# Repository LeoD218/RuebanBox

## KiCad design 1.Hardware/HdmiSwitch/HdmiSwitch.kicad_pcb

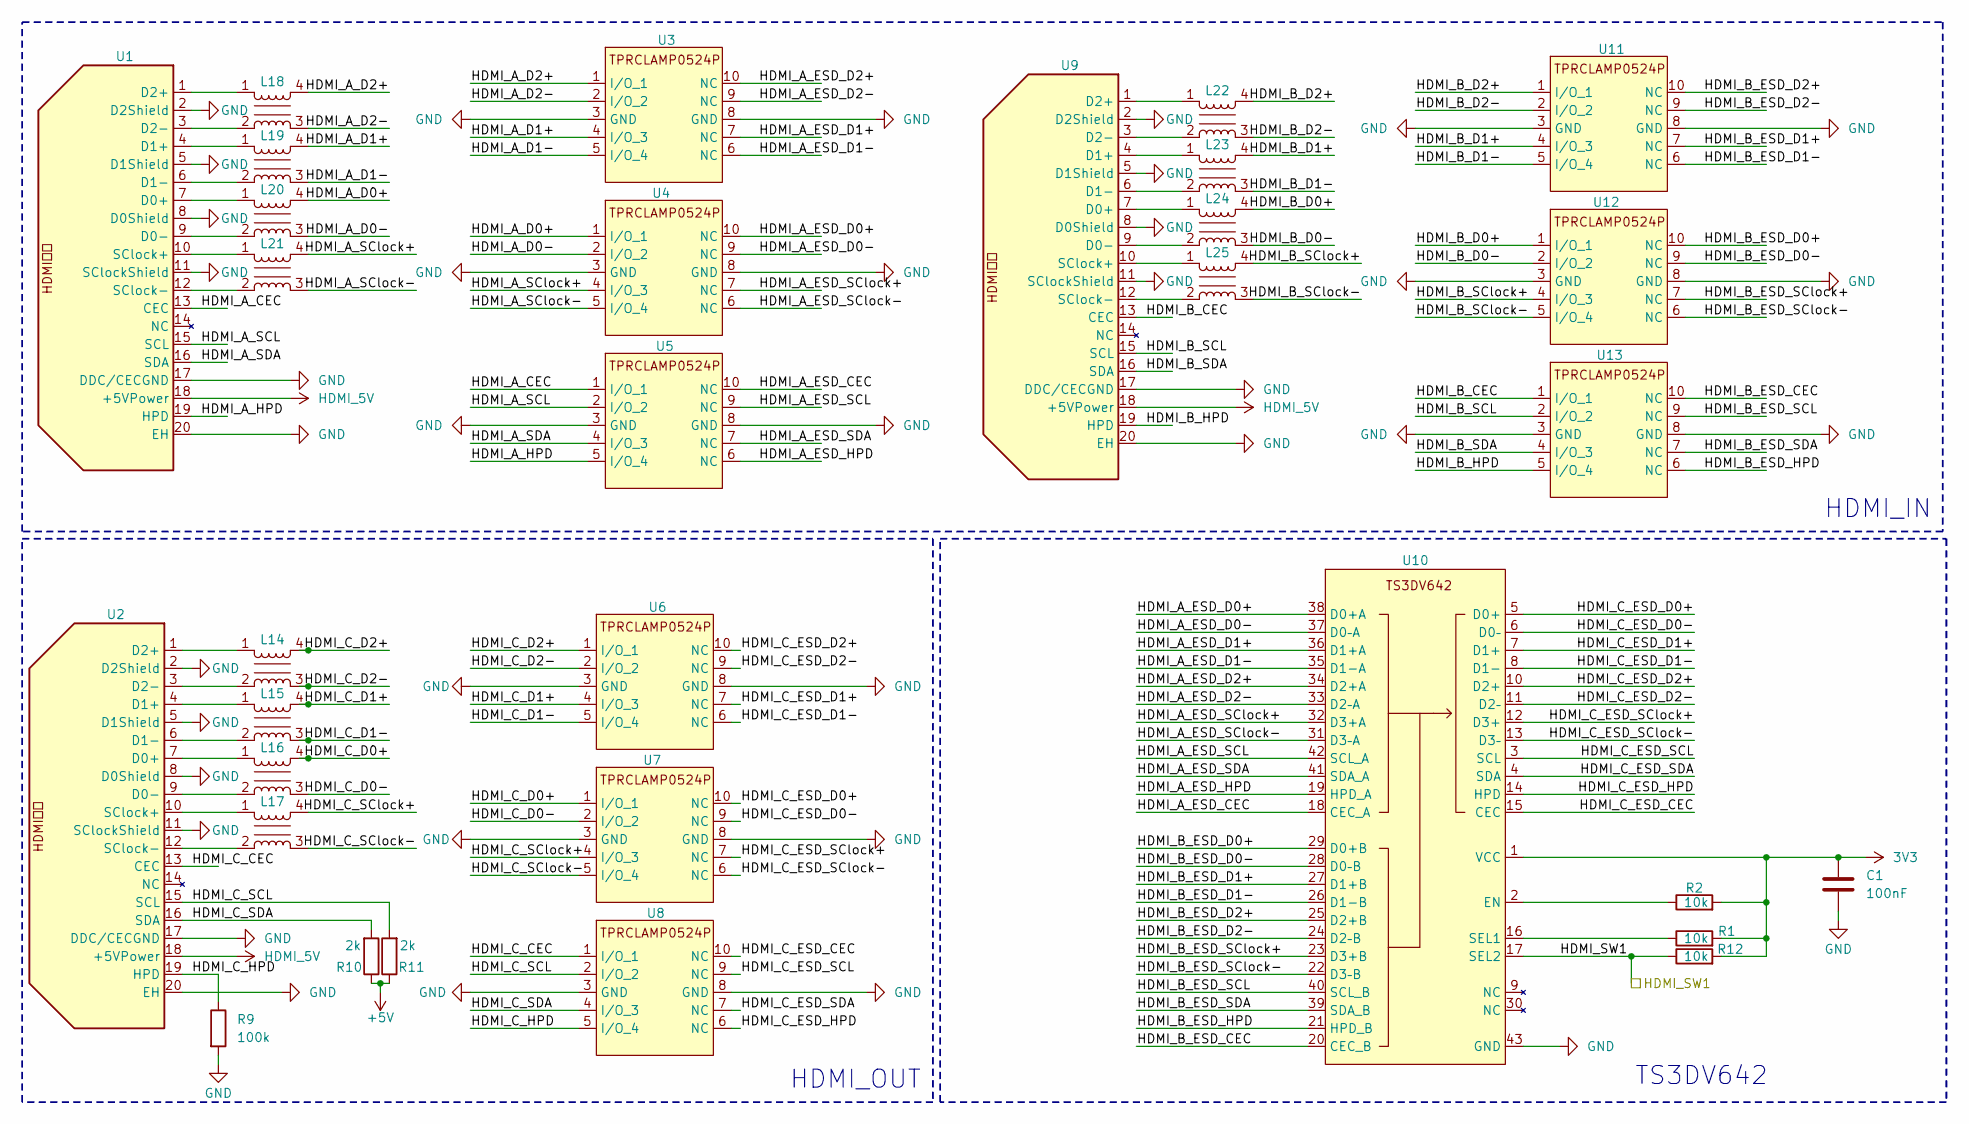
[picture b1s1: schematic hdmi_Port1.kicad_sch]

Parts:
C1: 100nF; C_0402_1005Metric
L14, L15, L16, L17, L18, L19, L20, L21, L22, L23, L24, L25: ACM2012-900-2P-T002
R1, R2: 10k; R_0402_1005Metric
R9: 100k; R_0402_1005Metric
R10, R11: 2k; R_0402_1005Metric
R12: 10k; C_0402_1005Metric
U1, U2, U9: HDMI侧插
U3, U4, U5, U6, U7, U8, U11, U12, U13: TPRCLAMP0524P
U10: TS3DV642

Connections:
3V3: C1.1, R1.2, R2.2, R12.2, U10.1 (VCC); also elsewhere on the board
+5V: R10.1, R11.1; also elsewhere on the board
/hdmi_Port1/HDMI_A_CEC: U1.13 (CEC), U5.1 (I/O_1)
/hdmi_Port1/HDMI_A_D0+: L20.4, U4.1 (I/O_1)
/hdmi_Port1/HDMI_A_D0-: L20.3, U4.2 (I/O_2)
/hdmi_Port1/HDMI_A_D1+: L19.4, U3.4 (I/O_3)
/hdmi_Port1/HDMI_A_D1-: L19.3, U3.5 (I/O_4)
/hdmi_Port1/HDMI_A_D2+: L18.4, U3.1 (I/O_1)
/hdmi_Port1/HDMI_A_D2-: L18.3, U3.2 (I/O_2)
/hdmi_Port1/HDMI_A_ESD_CEC: U5.10 (NC), U10.18 (CEC_A)
/hdmi_Port1/HDMI_A_ESD_D0+: U4.10 (NC), U10.38 (D0+A)
/hdmi_Port1/HDMI_A_ESD_D0-: U4.9 (NC), U10.37 (D0–A)
/hdmi_Port1/HDMI_A_ESD_D1+: U3.7 (NC), U10.36 (D1+A)
/hdmi_Port1/HDMI_A_ESD_D1-: U3.6 (NC), U10.35 (D1-A)
/hdmi_Port1/HDMI_A_ESD_D2+: U3.10 (NC), U10.34 (D2+A)
/hdmi_Port1/HDMI_A_ESD_D2-: U3.9 (NC), U10.33 (D2–A)
/hdmi_Port1/HDMI_A_ESD_HPD: U5.6 (NC), U10.19 (HPD_A)
/hdmi_Port1/HDMI_A_ESD_SCL: U5.9 (NC), U10.42 (SCL_A)
/hdmi_Port1/HDMI_A_ESD_SClock+: U4.7 (NC), U10.32 (D3+A)
/hdmi_Port1/HDMI_A_ESD_SClock-: U4.6 (NC), U10.31 (D3–A)
/hdmi_Port1/HDMI_A_ESD_SDA: U5.7 (NC), U10.41 (SDA_A)
/hdmi_Port1/HDMI_A_HPD: U1.19 (HPD), U5.5 (I/O_4)
/hdmi_Port1/HDMI_A_SCL: U1.15 (SCL), U5.2 (I/O_2)
/hdmi_Port1/HDMI_A_SClock+: L21.4, U4.4 (I/O_3)
/hdmi_Port1/HDMI_A_SClock-: L21.3, U4.5 (I/O_4)
/hdmi_Port1/HDMI_A_SDA: U1.16 (SDA), U5.4 (I/O_3)
/hdmi_Port1/HDMI_B_CEC: U9.13 (CEC), U13.1 (I/O_1)
/hdmi_Port1/HDMI_B_D0+: L24.4, U12.1 (I/O_1)
/hdmi_Port1/HDMI_B_D0-: L24.3, U12.2 (I/O_2)
/hdmi_Port1/HDMI_B_D1+: L23.4, U11.4 (I/O_3)
/hdmi_Port1/HDMI_B_D1-: L23.3, U11.5 (I/O_4)
/hdmi_Port1/HDMI_B_D2+: L22.4, U11.1 (I/O_1)
/hdmi_Port1/HDMI_B_D2-: L22.3, U11.2 (I/O_2)
/hdmi_Port1/HDMI_B_ESD_CEC: U10.20 (CEC_B), U13.10 (NC)
/hdmi_Port1/HDMI_B_ESD_D0+: U10.29 (D0+B), U12.10 (NC)
/hdmi_Port1/HDMI_B_ESD_D0-: U10.28 (D0–B), U12.9 (NC)
/hdmi_Port1/HDMI_B_ESD_D1+: U10.27 (D1+B), U11.7 (NC)
/hdmi_Port1/HDMI_B_ESD_D1-: U10.26 (D1-B), U11.6 (NC)
/hdmi_Port1/HDMI_B_ESD_D2+: U10.25 (D2+B), U11.10 (NC)
/hdmi_Port1/HDMI_B_ESD_D2-: U10.24 (D2–B), U11.9 (NC)
/hdmi_Port1/HDMI_B_ESD_HPD: U10.21 (HPD_B), U13.6 (NC)
/hdmi_Port1/HDMI_B_ESD_SCL: U10.40 (SCL_B), U13.9 (NC)
/hdmi_Port1/HDMI_B_ESD_SClock+: U10.23 (D3+B), U12.7 (NC)
/hdmi_Port1/HDMI_B_ESD_SClock-: U10.22 (D3–B), U12.6 (NC)
/hdmi_Port1/HDMI_B_ESD_SDA: U10.39 (SDA_B), U13.7 (NC)
/hdmi_Port1/HDMI_B_HPD: U9.19 (HPD), U13.5 (I/O_4)
/hdmi_Port1/HDMI_B_SCL: U9.15 (SCL), U13.2 (I/O_2)
/hdmi_Port1/HDMI_B_SClock+: L25.4, U12.4 (I/O_3)
/hdmi_Port1/HDMI_B_SClock-: L25.3, U12.5 (I/O_4)
/hdmi_Port1/HDMI_B_SDA: U9.16 (SDA), U13.4 (I/O_3)
/hdmi_Port1/HDMI_C_CEC: U2.13 (CEC), U8.1 (I/O_1)
/hdmi_Port1/HDMI_C_D0+: L16.4, U7.1 (I/O_1)
/hdmi_Port1/HDMI_C_D0-: L16.3, U7.2 (I/O_2)
/hdmi_Port1/HDMI_C_D1+: L15.4, U6.4 (I/O_3)
/hdmi_Port1/HDMI_C_D1-: L15.3, U6.5 (I/O_4)
/hdmi_Port1/HDMI_C_D2+: L14.4, U6.1 (I/O_1)
/hdmi_Port1/HDMI_C_D2-: L14.3, U6.2 (I/O_2)
/hdmi_Port1/HDMI_C_ESD_CEC: U8.10 (NC), U10.15 (CEC)
/hdmi_Port1/HDMI_C_ESD_D0+: U7.10 (NC), U10.5 (D0+)
/hdmi_Port1/HDMI_C_ESD_D0-: U7.9 (NC), U10.6 (D0–)
/hdmi_Port1/HDMI_C_ESD_D1+: U6.7 (NC), U10.7 (D1+)
/hdmi_Port1/HDMI_C_ESD_D1-: U6.6 (NC), U10.8 (D1-)
/hdmi_Port1/HDMI_C_ESD_D2+: U6.10 (NC), U10.10 (D2+)
/hdmi_Port1/HDMI_C_ESD_D2-: U6.9 (NC), U10.11 (D2–)
/hdmi_Port1/HDMI_C_ESD_HPD: U8.6 (NC), U10.14 (HPD)
/hdmi_Port1/HDMI_C_ESD_SCL: U8.9 (NC), U10.3 (SCL)
/hdmi_Port1/HDMI_C_ESD_SClock+: U7.7 (NC), U10.12 (D3+)
/hdmi_Port1/HDMI_C_ESD_SClock-: U7.6 (NC), U10.13 (D3–)
/hdmi_Port1/HDMI_C_ESD_SDA: U8.7 (NC), U10.4 (SDA)
/hdmi_Port1/HDMI_C_HPD: R9.1, U2.19 (HPD), U8.5 (I/O_4)
/hdmi_Port1/HDMI_C_SCL: R11.2, U2.15 (SCL), U8.2 (I/O_2)
/hdmi_Port1/HDMI_C_SClock+: L17.4, U7.4 (I/O_3)
/hdmi_Port1/HDMI_C_SClock-: L17.3, U7.5 (I/O_4)
/hdmi_Port1/HDMI_C_SDA: R10.2, U2.16 (SDA), U8.4 (I/O_3)
/hdmi_Port1/HDMI_SW1: R12.1, U10.17 (SEL2); also elsewhere on the board
GND: C1.2, R9.2, U1.2 (D2Shield), U1.5 (D1Shield), U1.8 (D0Shield), U1.11 (SClockShield), U1.17 (DDC/CECGND), U1.20 (EH), U2.2 (D2Shield), U2.5 (D1Shield), U2.8 (D0Shield), U2.11 (SClockShield), U2.17 (DDC/CECGND), U2.20 (EH), U3.3 (GND), U3.8 (GND), U4.3 (GND), U4.8 (GND), U5.3 (GND), U5.8 (GND), U6.3 (GND), U6.8 (GND), U7.3 (GND), U7.8 (GND), U8.3 (GND), U8.8 (GND), U9.2 (D2Shield), U9.5 (D1Shield), U9.8 (D0Shield), U9.11 (SClockShield), U9.17 (DDC/CECGND), U9.20 (EH), U10.43 (GND), U11.3 (GND), U11.8 (GND), U12.3 (GND), U12.8 (GND), U13.3 (GND), U13.8 (GND); also elsewhere on the board
HDMI_5V: U1.18 (+5VPower), U2.18 (+5VPower), U9.18 (+5VPower); also elsewhere on the board
unnamed: L20.1, U1.7 (D0+)
unnamed: L20.2, U1.9 (D0-)
unnamed: L19.1, U1.4 (D1+)
unnamed: L19.2, U1.6 (D1-)
unnamed: L18.1, U1.1 (D2+)
unnamed: L18.2, U1.3 (D2-)
unnamed: L21.1, U1.10 (SClock+)
unnamed: L21.2, U1.12 (SClock-)
unnamed: L16.1, U2.7 (D0+)
unnamed: L16.2, U2.9 (D0-)
unnamed: L15.1, U2.4 (D1+)
unnamed: L15.2, U2.6 (D1-)
unnamed: L14.1, U2.1 (D2+)
unnamed: L14.2, U2.3 (D2-)
unnamed: L17.1, U2.10 (SClock+)
unnamed: L17.2, U2.12 (SClock-)
unnamed: L24.1, U9.7 (D0+)
unnamed: L24.2, U9.9 (D0-)
unnamed: L23.1, U9.4 (D1+)
unnamed: L23.2, U9.6 (D1-)
unnamed: L22.1, U9.1 (D2+)
unnamed: L22.2, U9.3 (D2-)
unnamed: L25.1, U9.10 (SClock+)
unnamed: L25.2, U9.12 (SClock-)
unnamed: R2.1, U10.2 (EN)
unnamed: R1.1, U10.16 (SEL1)

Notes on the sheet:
HDMI_IN
TS3DV642
HDMI_OUT

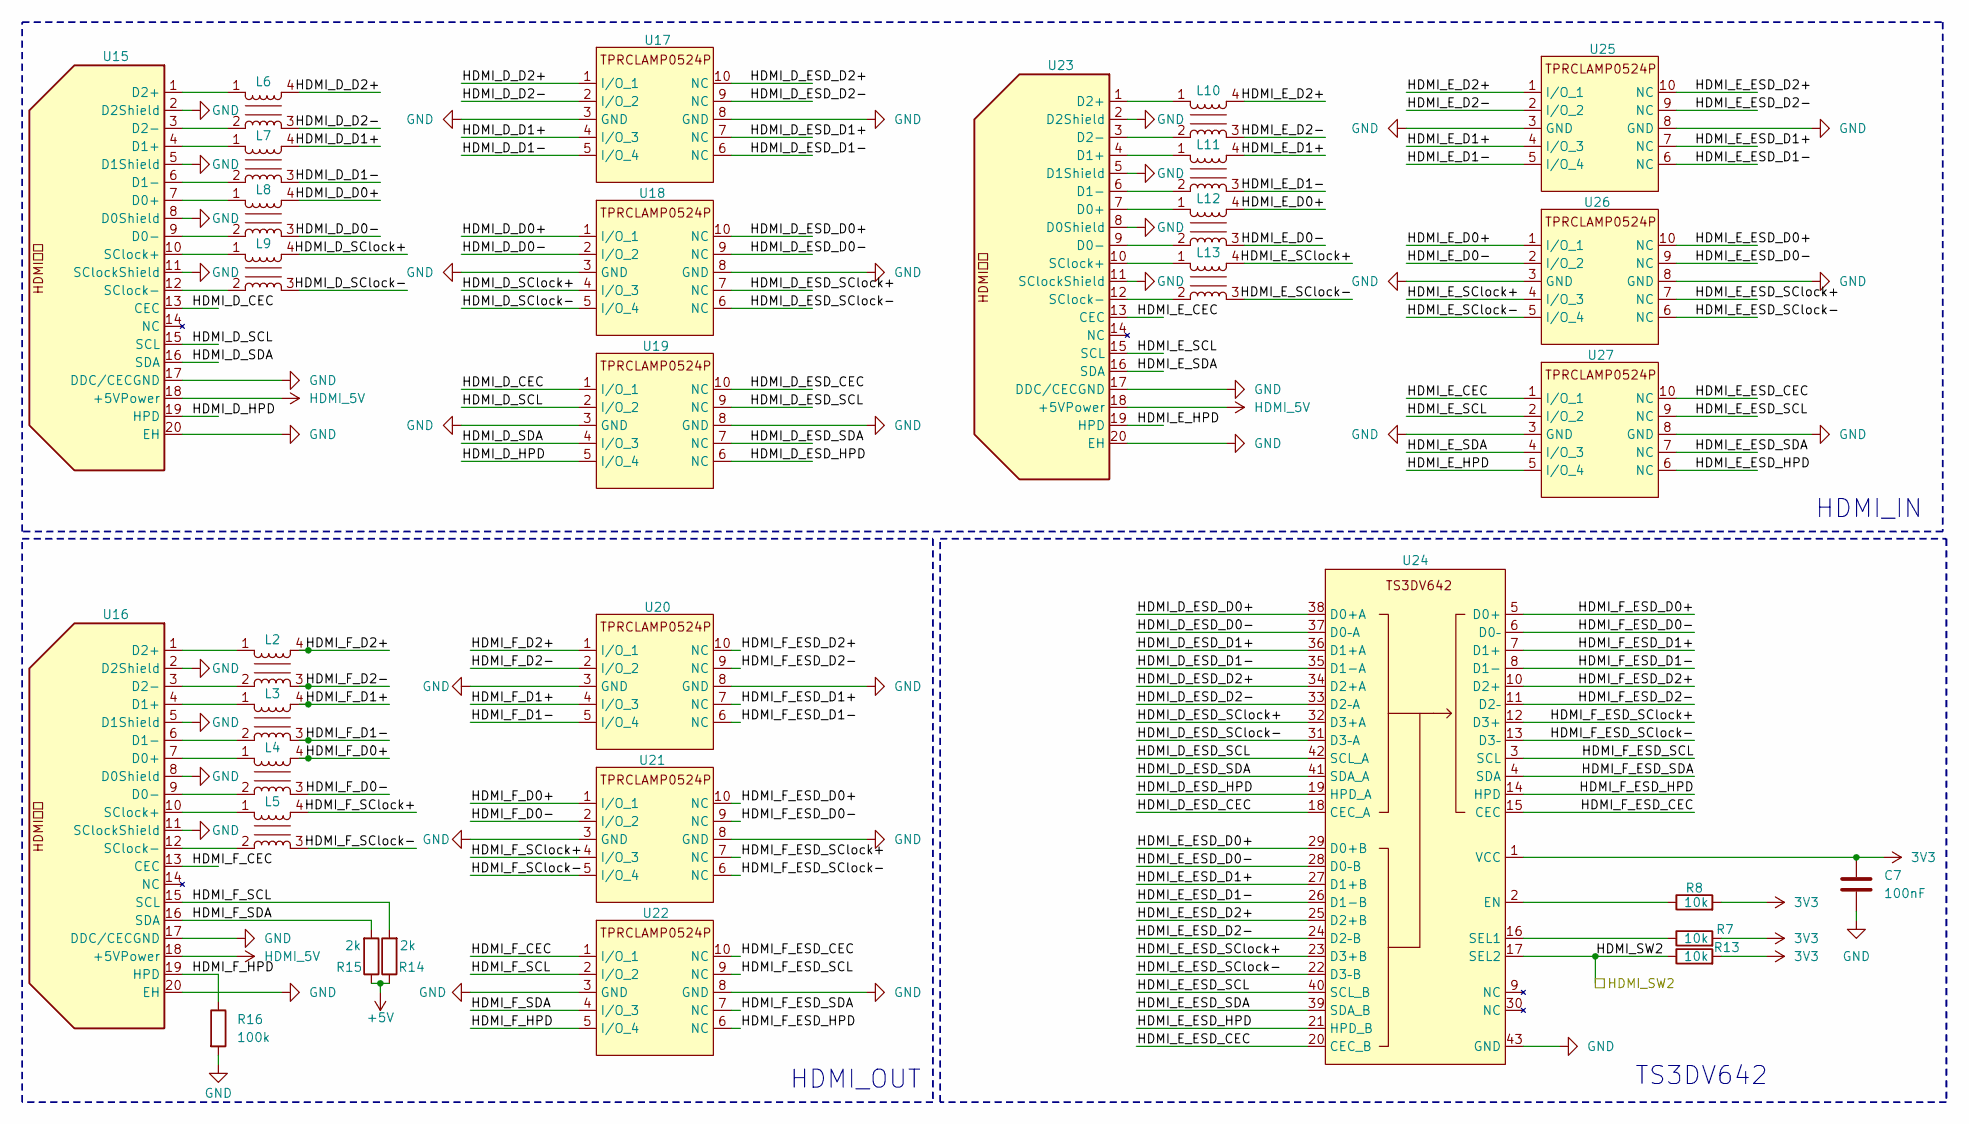
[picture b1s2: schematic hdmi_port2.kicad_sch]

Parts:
C7: 100nF; C_0402_1005Metric
L2, L3, L4, L5, L6, L7, L8, L9, L10, L11, L12, L13: ACM2012-900-2P-T002
R7, R8, R13: 10k; R_0402_1005Metric
R14: 2k; C_0402_1005Metric
R15: 2k; R_0402_1005Metric
R16: 100k; R_0402_1005Metric
U15, U16, U23: HDMI侧插
U17, U18, U19, U20, U21, U22, U25, U26, U27: TPRCLAMP0524P
U24: TS3DV642

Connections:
3V3: C7.1, R7.2, R8.2, R13.2, U24.1 (VCC); also elsewhere on the board
+5V: R14.1, R15.1; also elsewhere on the board
/hdmi_port2/HDMI_D_CEC: U15.13 (CEC), U19.1 (I/O_1)
/hdmi_port2/HDMI_D_D0+: L8.4, U18.1 (I/O_1)
/hdmi_port2/HDMI_D_D0-: L8.3, U18.2 (I/O_2)
/hdmi_port2/HDMI_D_D1+: L7.4, U17.4 (I/O_3)
/hdmi_port2/HDMI_D_D1-: L7.3, U17.5 (I/O_4)
/hdmi_port2/HDMI_D_D2+: L6.4, U17.1 (I/O_1)
/hdmi_port2/HDMI_D_D2-: L6.3, U17.2 (I/O_2)
/hdmi_port2/HDMI_D_ESD_CEC: U19.10 (NC), U24.18 (CEC_A)
/hdmi_port2/HDMI_D_ESD_D0+: U18.10 (NC), U24.38 (D0+A)
/hdmi_port2/HDMI_D_ESD_D0-: U18.9 (NC), U24.37 (D0–A)
/hdmi_port2/HDMI_D_ESD_D1+: U17.7 (NC), U24.36 (D1+A)
/hdmi_port2/HDMI_D_ESD_D1-: U17.6 (NC), U24.35 (D1-A)
/hdmi_port2/HDMI_D_ESD_D2+: U17.10 (NC), U24.34 (D2+A)
/hdmi_port2/HDMI_D_ESD_D2-: U17.9 (NC), U24.33 (D2–A)
/hdmi_port2/HDMI_D_ESD_HPD: U19.6 (NC), U24.19 (HPD_A)
/hdmi_port2/HDMI_D_ESD_SCL: U19.9 (NC), U24.42 (SCL_A)
/hdmi_port2/HDMI_D_ESD_SClock+: U18.7 (NC), U24.32 (D3+A)
/hdmi_port2/HDMI_D_ESD_SClock-: U18.6 (NC), U24.31 (D3–A)
/hdmi_port2/HDMI_D_ESD_SDA: U19.7 (NC), U24.41 (SDA_A)
/hdmi_port2/HDMI_D_HPD: U15.19 (HPD), U19.5 (I/O_4)
/hdmi_port2/HDMI_D_SCL: U15.15 (SCL), U19.2 (I/O_2)
/hdmi_port2/HDMI_D_SClock+: L9.4, U18.4 (I/O_3)
/hdmi_port2/HDMI_D_SClock-: L9.3, U18.5 (I/O_4)
/hdmi_port2/HDMI_D_SDA: U15.16 (SDA), U19.4 (I/O_3)
/hdmi_port2/HDMI_E_CEC: U23.13 (CEC), U27.1 (I/O_1)
/hdmi_port2/HDMI_E_D0+: L12.4, U26.1 (I/O_1)
/hdmi_port2/HDMI_E_D0-: L12.3, U26.2 (I/O_2)
/hdmi_port2/HDMI_E_D1+: L11.4, U25.4 (I/O_3)
/hdmi_port2/HDMI_E_D1-: L11.3, U25.5 (I/O_4)
/hdmi_port2/HDMI_E_D2+: L10.4, U25.1 (I/O_1)
/hdmi_port2/HDMI_E_D2-: L10.3, U25.2 (I/O_2)
/hdmi_port2/HDMI_E_ESD_CEC: U24.20 (CEC_B), U27.10 (NC)
/hdmi_port2/HDMI_E_ESD_D0+: U24.29 (D0+B), U26.10 (NC)
/hdmi_port2/HDMI_E_ESD_D0-: U24.28 (D0–B), U26.9 (NC)
/hdmi_port2/HDMI_E_ESD_D1+: U24.27 (D1+B), U25.7 (NC)
/hdmi_port2/HDMI_E_ESD_D1-: U24.26 (D1-B), U25.6 (NC)
/hdmi_port2/HDMI_E_ESD_D2+: U24.25 (D2+B), U25.10 (NC)
/hdmi_port2/HDMI_E_ESD_D2-: U24.24 (D2–B), U25.9 (NC)
/hdmi_port2/HDMI_E_ESD_HPD: U24.21 (HPD_B), U27.6 (NC)
/hdmi_port2/HDMI_E_ESD_SCL: U24.40 (SCL_B), U27.9 (NC)
/hdmi_port2/HDMI_E_ESD_SClock+: U24.23 (D3+B), U26.7 (NC)
/hdmi_port2/HDMI_E_ESD_SClock-: U24.22 (D3–B), U26.6 (NC)
/hdmi_port2/HDMI_E_ESD_SDA: U24.39 (SDA_B), U27.7 (NC)
/hdmi_port2/HDMI_E_HPD: U23.19 (HPD), U27.5 (I/O_4)
/hdmi_port2/HDMI_E_SCL: U23.15 (SCL), U27.2 (I/O_2)
/hdmi_port2/HDMI_E_SClock+: L13.4, U26.4 (I/O_3)
/hdmi_port2/HDMI_E_SClock-: L13.3, U26.5 (I/O_4)
/hdmi_port2/HDMI_E_SDA: U23.16 (SDA), U27.4 (I/O_3)
/hdmi_port2/HDMI_F_CEC: U16.13 (CEC), U22.1 (I/O_1)
/hdmi_port2/HDMI_F_D0+: L4.4, U21.1 (I/O_1)
/hdmi_port2/HDMI_F_D0-: L4.3, U21.2 (I/O_2)
/hdmi_port2/HDMI_F_D1+: L3.4, U20.4 (I/O_3)
/hdmi_port2/HDMI_F_D1-: L3.3, U20.5 (I/O_4)
/hdmi_port2/HDMI_F_D2+: L2.4, U20.1 (I/O_1)
/hdmi_port2/HDMI_F_D2-: L2.3, U20.2 (I/O_2)
/hdmi_port2/HDMI_F_ESD_CEC: U22.10 (NC), U24.15 (CEC)
/hdmi_port2/HDMI_F_ESD_D0+: U21.10 (NC), U24.5 (D0+)
/hdmi_port2/HDMI_F_ESD_D0-: U21.9 (NC), U24.6 (D0–)
/hdmi_port2/HDMI_F_ESD_D1+: U20.7 (NC), U24.7 (D1+)
/hdmi_port2/HDMI_F_ESD_D1-: U20.6 (NC), U24.8 (D1-)
/hdmi_port2/HDMI_F_ESD_D2+: U20.10 (NC), U24.10 (D2+)
/hdmi_port2/HDMI_F_ESD_D2-: U20.9 (NC), U24.11 (D2–)
/hdmi_port2/HDMI_F_ESD_HPD: U22.6 (NC), U24.14 (HPD)
/hdmi_port2/HDMI_F_ESD_SCL: U22.9 (NC), U24.3 (SCL)
/hdmi_port2/HDMI_F_ESD_SClock+: U21.7 (NC), U24.12 (D3+)
/hdmi_port2/HDMI_F_ESD_SClock-: U21.6 (NC), U24.13 (D3–)
/hdmi_port2/HDMI_F_ESD_SDA: U22.7 (NC), U24.4 (SDA)
/hdmi_port2/HDMI_F_HPD: R16.1, U16.19 (HPD), U22.5 (I/O_4)
/hdmi_port2/HDMI_F_SCL: R14.2, U16.15 (SCL), U22.2 (I/O_2)
/hdmi_port2/HDMI_F_SClock+: L5.4, U21.4 (I/O_3)
/hdmi_port2/HDMI_F_SClock-: L5.3, U21.5 (I/O_4)
/hdmi_port2/HDMI_F_SDA: R15.2, U16.16 (SDA), U22.4 (I/O_3)
/hdmi_port2/HDMI_SW2: R13.1, U24.17 (SEL2); also elsewhere on the board
GND: C7.2, R16.2, U15.2 (D2Shield), U15.5 (D1Shield), U15.8 (D0Shield), U15.11 (SClockShield), U15.17 (DDC/CECGND), U15.20 (EH), U16.2 (D2Shield), U16.5 (D1Shield), U16.8 (D0Shield), U16.11 (SClockShield), U16.17 (DDC/CECGND), U16.20 (EH), U17.3 (GND), U17.8 (GND), U18.3 (GND), U18.8 (GND), U19.3 (GND), U19.8 (GND), U20.3 (GND), U20.8 (GND), U21.3 (GND), U21.8 (GND), U22.3 (GND), U22.8 (GND), U23.2 (D2Shield), U23.5 (D1Shield), U23.8 (D0Shield), U23.11 (SClockShield), U23.17 (DDC/CECGND), U23.20 (EH), U24.43 (GND), U25.3 (GND), U25.8 (GND), U26.3 (GND), U26.8 (GND), U27.3 (GND), U27.8 (GND); also elsewhere on the board
HDMI_5V: U15.18 (+5VPower), U16.18 (+5VPower), U23.18 (+5VPower); also elsewhere on the board
unnamed: L8.1, U15.7 (D0+)
unnamed: L8.2, U15.9 (D0-)
unnamed: L7.1, U15.4 (D1+)
unnamed: L7.2, U15.6 (D1-)
unnamed: L6.1, U15.1 (D2+)
unnamed: L6.2, U15.3 (D2-)
unnamed: L9.1, U15.10 (SClock+)
unnamed: L9.2, U15.12 (SClock-)
unnamed: L4.1, U16.7 (D0+)
unnamed: L4.2, U16.9 (D0-)
unnamed: L3.1, U16.4 (D1+)
unnamed: L3.2, U16.6 (D1-)
unnamed: L2.1, U16.1 (D2+)
unnamed: L2.2, U16.3 (D2-)
unnamed: L5.1, U16.10 (SClock+)
unnamed: L5.2, U16.12 (SClock-)
unnamed: L12.1, U23.7 (D0+)
unnamed: L12.2, U23.9 (D0-)
unnamed: L11.1, U23.4 (D1+)
unnamed: L11.2, U23.6 (D1-)
unnamed: L10.1, U23.1 (D2+)
unnamed: L10.2, U23.3 (D2-)
unnamed: L13.1, U23.10 (SClock+)
unnamed: L13.2, U23.12 (SClock-)
unnamed: R8.1, U24.2 (EN)
unnamed: R7.1, U24.16 (SEL1)

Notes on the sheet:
TS3DV642
HDMI_OUT
HDMI_IN

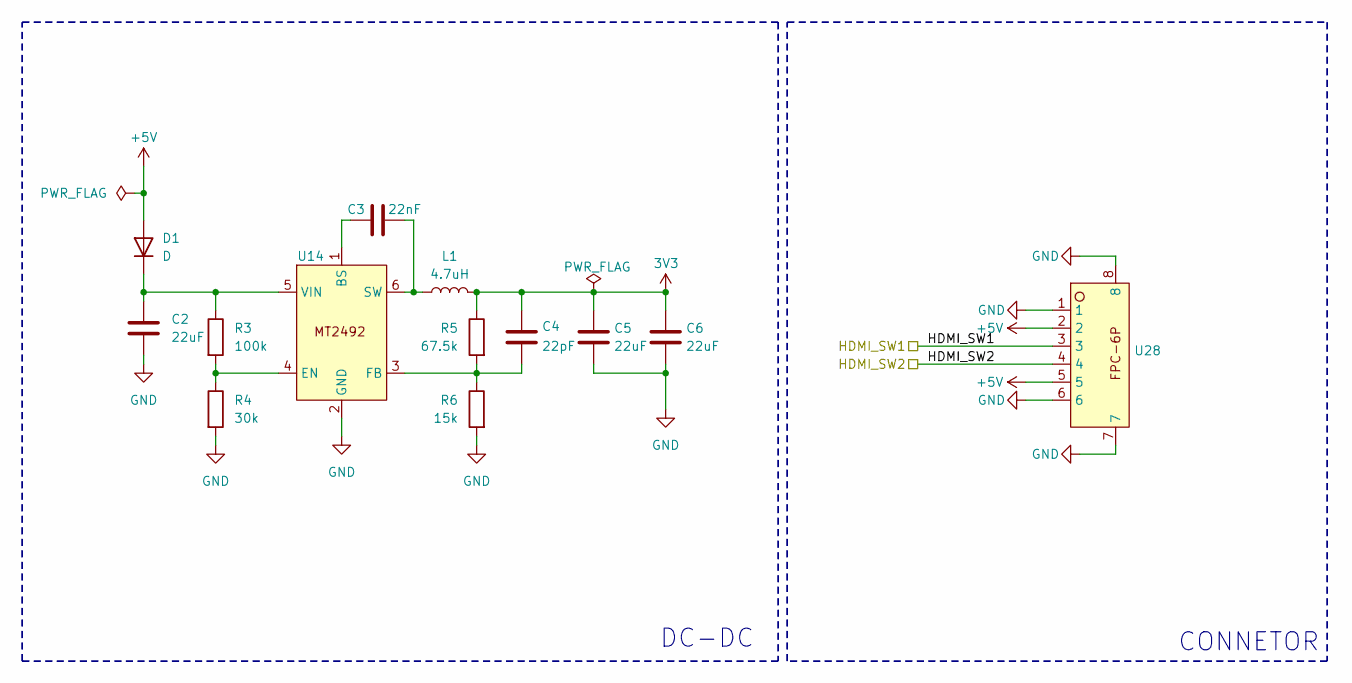
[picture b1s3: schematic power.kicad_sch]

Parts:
C2, C5, C6: 22uF; C_0805_2012Metric
C3: 22nF; C_0402_1005Metric
C4: 22pF; C_0402_1005Metric
D1: D; 二极管
L1: 4.7uH; CD32
R3: 100k; R_0402_1005Metric
R4: 30k; R_0402_1005Metric
R5: 67.5k; R_0402_1005Metric
R6: 15k; R_0402_1005Metric
U14: SOT-23-6
U28: FPC座子6P翻盖下接

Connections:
3V3: C4.1, C5.1, C6.1, L1.2, R5.1; also elsewhere on the board
+5V: D1.2 (A), U28.2, U28.5; also elsewhere on the board
/hdmi_Port1/HDMI_SW1: U28.3; also elsewhere on the board
/hdmi_port2/HDMI_SW2: U28.4; also elsewhere on the board
GND: C2.2, C5.2, C6.2, R4.2, R6.2, U14.2 (GND), U28.1, U28.6, U28.7, U28.8; also elsewhere on the board
unnamed: C2.1, D1.1 (K), R3.1, U14.5 (VIN)
unnamed: C3.1, U14.1 (BS)
unnamed: R3.2, R4.1, U14.4 (EN)
unnamed: C4.2, R5.2, R6.1, U14.3 (FB)
unnamed: C3.2, L1.1, U14.6 (SW)

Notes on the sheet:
DC-DC
CONNETOR

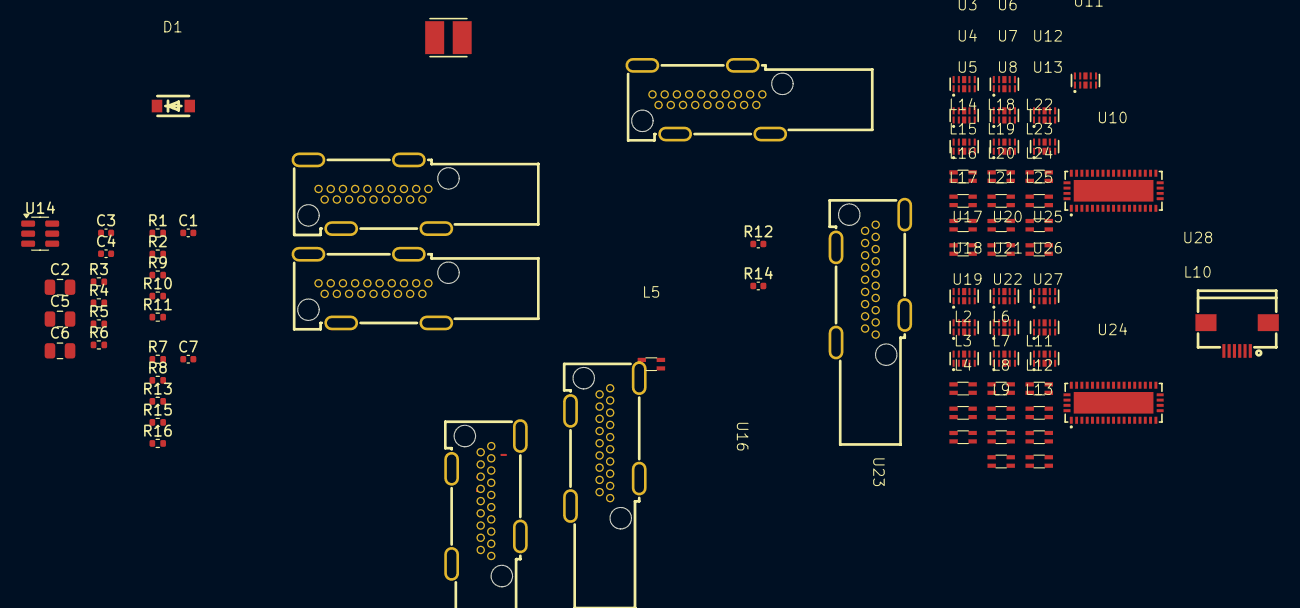
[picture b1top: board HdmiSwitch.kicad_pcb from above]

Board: 2 copper layers, 77 parts (0 on the bottom side), 207 nets.

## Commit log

2024-07-10 绘制了交换机模块的部分原理图
2024-07-12 绘制了USBHUB /d/projects/RuebanBox (main)电路的原理图
2024-07-14 为HDMISwitch模块添加了封装模型
